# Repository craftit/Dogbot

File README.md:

# Dogbot

[DogBot] is a quadruped robot developed by [React AI] as a platform for researching robotics, AI and more.

The Dogbot repository contains CAD designs, along with software for higher-level systems for control and operation of the [React AI] DogBot robot via [ROS].  It utilises the lower-level motor control firmware in the corresponding [Firmware] repository for interaction with the physical DogBot.

# Installation

This code has been tested for installation and operation on Ubuntu Linux.

[ROS] must be installed; the code has been tested against the Kinetic release.  The repository contains a [catkin](http://wiki.ros.org/catkin) workspace under [Software/ROS](./Software/ROS), which should be built with `catkin build`

You may need to install the packages `ros-kinetic-rosparam-shortcuts ros-kinetic-ros-control ros-kinetic-ros-controllers` 

# Operation via Firmware and ROS

## Home the motors

The motors must be ‘homed’, i.e. know their absolute position, before they can be controlled via the ROS driver, hence they must first be controlled via the UI as described in the [Firmware] repo.

**Note:** complete the Firmware UI steps before starting the ROS components.  The hardware interface node in ROS will send conflicting signals if it is operational while the UI tries to alter the motor positions.

## Quick Start

To get started with ROS control, build and source the code then run `dogbot_hardware.launch`

```bat
cd Software/ROS
catkin build
source devel/setup.bash
roslaunch dogbot_control dogbot_hardware.launch
```

This launches a hardware interface node of type dogbot_control/dogbot_hw_main, which uses the [ros_control](http://wiki.ros.org/controller_manager) package to spawn and interact with ROS controllers.  This provides a framework for different controller types, as well as standardising interactions with Gazebo and RViz.

If you are controlling other equipment you may require a different launch file, such as testrig_hardware.launch

## Further ROS Control

The motors can now be controlled by interacting directly with ROS topics or via ROS nodes. Further details are in the ROS directory [readme file](./Software/ROS)

# Contributing

If you have any problems with the contents of either repository, or have a question about [DogBot], please feel free to [contact us](https://www.reactai.com/)

If you wish to contribute please fork the project on GitHub.  More details on contributing to follow.

# License

details to follow

[DogBot]: https://www.reactai.com/dog-bot/
[React AI]: https://www.reactai.com
[ROS]: http://www.ros.org
[Firmware]: https://github.com/craftit/BMC2-Firmware

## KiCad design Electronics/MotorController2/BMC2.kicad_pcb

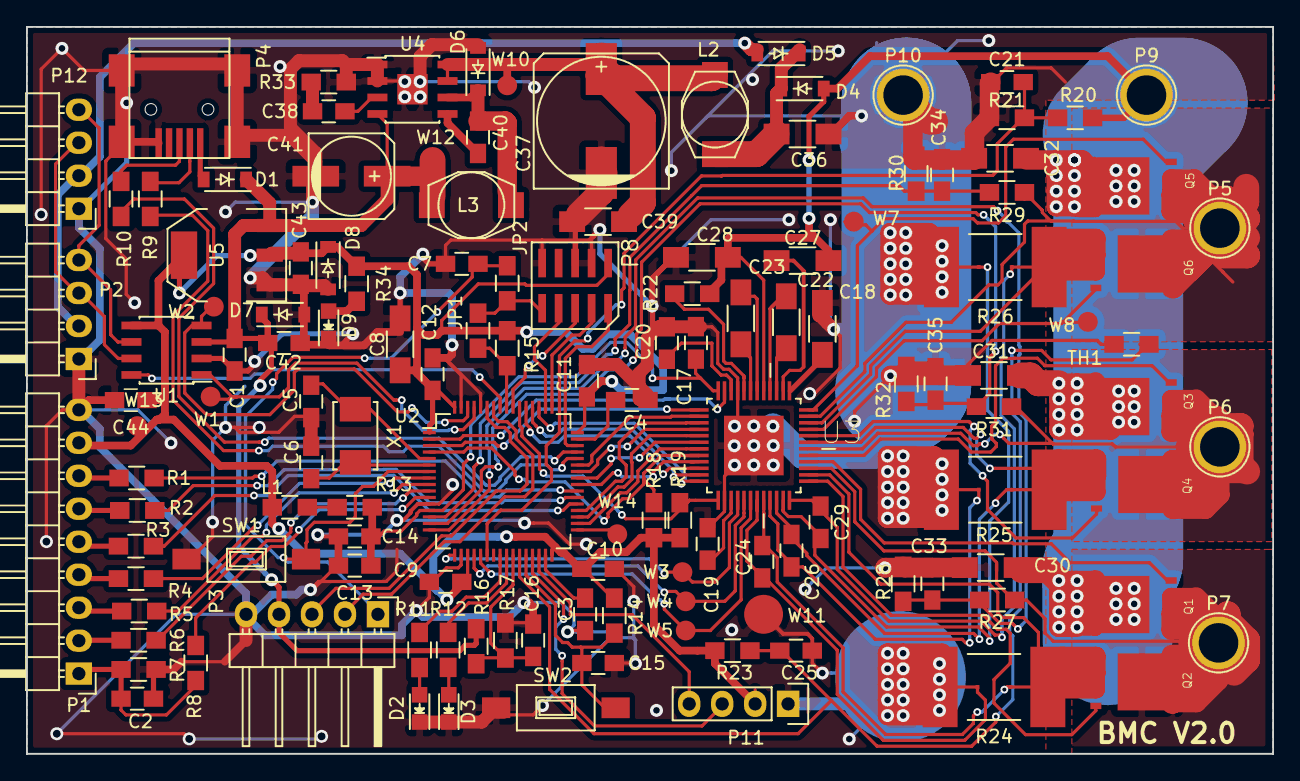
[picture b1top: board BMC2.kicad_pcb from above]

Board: 2 copper layers, 96.0 x 56.0 mm, 131 parts (0 on the bottom side), 109 nets.

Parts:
C1, C44: 0.1uf (6V min); C_0805_HandSoldering
C2: 0.1uF; C_0805_HandSoldering
C3, C4: 2.2uf; C_0805_HandSoldering
C5, C6: 15pF; C_0805_HandSoldering
C7, C10, C11, C12: 100nf; C_0805_HandSoldering
C8: 4.7uf; C_1206_HandSoldering
C9: 100nf 5V; C_0805_HandSoldering
C13: 10nf; C_0805_HandSoldering
C14: 1uf; C_0805_HandSoldering
C15, C16, C21, C25: 0.1uF 5V; C_0805_HandSoldering
C17: 1uF 4V; C_0805_HandSoldering
C18: 1uf 16V; C_1206_HandSoldering
C19, C20: 1uf 6.3V; C_0805_HandSoldering
C22: 0.047uf 90V; C_1206_HandSoldering
C23: 0.047uf 45v; C_1206_HandSoldering
C24, C26: 1nF 5V; C_0805_HandSoldering
C27: 2.2uf 16V; C_1206_HandSoldering
C28: 4.7uF 45V; C_1206_HandSoldering
C29: 1nf 5V; C_0805_HandSoldering
C30, C31, C32: 1uF 50V; C_1206_HandSoldering
C33, C34, C35: 30pF 5V; C_0805_HandSoldering
C36, C39: 220nF 60V; C_1206_HandSoldering
C37: 100uF 60V; c_elec_10x10.5
C38: 22nF 6V; C_0805_HandSoldering
C40, C42: 220nF 6V; C_0805_HandSoldering
C41: 100uF 6V; c_elec_6.3x5.8
C43: 1uF 4V min; C_0805_HandSoldering
D1: 10V; SOD-123
D2: GREEN LED; LED_0805
D3: RED LED; LED_0805
D4, D5: 60V 2A; SOD-123
D6: 50V; SOD-123
D7: 5.4V; SOD-123
D8: 3.6V; SOD-123
D9: LED; LED_0805
JP1: Jumper_NO_Small; R_0805_HandSoldering
JP2: Jumper_NC_Small; R_0805_HandSoldering
L1: 10uH; R_0805_HandSoldering
L2, L3: 47uH; SELF-WE-PD3S
P1: Sensor; Pin_Header_Angled_1x09
P2, P12: CAN; Pin_Header_Angled_1x04
P3: DATA; Pin_Header_Angled_1x05
P4: USB_OTG; USB_Mini-B
P5: PhaseA; 1pin
P6: PhaseB; 1pin
P7: PhaseC; 1pin
P8: CONN_02X05; SMT-HDR-10
P9: VSUPPLY; 1pin
P10: GND; 1pin
P11: I2C; Pin_Header_Straight_1x04
Q1, Q2, Q3, Q4, Q5, Q6: BSC016N06NS; SON127P532X615X110-8N
R1, R2, R3, R4, R5, R6, R8: 1k; R_0805_HandSoldering
R7: 10k; R_0805_HandSoldering
R9, R10: 22R; R_0805_HandSoldering
R11, R12, R22, R34: 100R; R_0805_HandSoldering
R13: 10; R_0805_HandSoldering
R14, R15, R16, R17, R18, R19, R23: 10K; R_0805_HandSoldering
R20, R27, R29, R31: 39K; R_0805_HandSoldering
R21, R28, R30, R32: 3K; R_0805_HandSoldering
R24, R25, R26: R001; R_PSR400_SENSE
R33: 22k; R_0805_HandSoldering
SW1: RESET; SW_SPST_FSMSM
SW2: CAL; SW_SPST_FSMSM
TH1: THERMISTOR; R_0805_HandSoldering
U1: TJA1042T/3; SOIC-8_3.9x4.9mm_Pitch1.27mm
U2: STM32F205RBTx; LQFP-64_10x10mm_Pitch0.5mm
U3: DRV8305; QFP50P900X900X120-49N
U4: IFX91041EJV50; SOIC-8-1EP_3.9x4.9mm_Pitch1.27mm
U5: TC2117-3.3V; SOT-223
W1: CAN_TX; Measurement_Point_Round-SMD-Pad_Small
W2: CAN_RX; Measurement_Point_Round-SMD-Pad_Small
W3: ISenseA; Measurement_Point_Round-SMD-Pad_Small
W4: ISenseB; Measurement_Point_Round-SMD-Pad_Small
W5: ISenseC; Measurement_Point_Round-SMD-Pad_Small
W7: GHA; Measurement_Point_Round-SMD-Pad_Small
W8: GLA; Measurement_Point_Round-SMD-Pad_Small
W10: DSUP; Measurement_Point_Round-SMD-Pad_Small
W11: GND; Measurement_Point_Round-SMD-Pad_Big
W12: 5V; Measurement_Point_Round-SMD-Pad_Small
W13: 3V3; Measurement_Point_Round-SMD-Pad_Small
W14: PB12; Measurement_Point_Round-SMD-Pad_Small
X1: 8MHz; ABM3

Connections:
+3.3VADC: C13.1, C14.1, C17.1, R13.1, U2.13, U3.48
+3V3: C8.1, C9.1, C10.1, C11.1, C12.1, C43.1, C44.1, D8.1, L1.1, P1.8, P8.1, P11.2, R14.1, R15.2, R18.1, R19.1, R23.1, R34.1, U1.5, U2.1, U2.19, U2.32, U2.48, U2.64, U5.2, U5.4, W13.1
+5V: C1.1, C41.1, C42.1, D1.1, D7.1, L3.1, P3.4, R16.1, U1.3, U4.4, U5.3, W12.1
+8V: D5.2, P2.2, P12.2
+36V: C27.2, C28.1, C30.1, C31.1, C32.1, D4.2, P9.1, Q1.5, Q1.6, Q1.7, Q1.8, Q3.5, Q3.6, Q3.7, Q3.8, Q5.5, Q5.6, Q5.7, Q5.8, R20.1, R22.1, U3.41
/Controller/CAN_RX: U1.4, U2.62, W2.1
/Controller/CAN_STBY: U1.8, U2.57
/Controller/CAN_TX: U1.1, U2.61, W1.1
/Controller/EN_GATE: U2.3, U3.1
/Controller/EndStop1: R3.1, U2.37
/Controller/EndStop2: R2.1, U2.38
/Controller/FAULT: R18.2, U2.4, U3.8
/Controller/HallA: R4.1, U2.8
/Controller/HallB: R5.1, U2.9
/Controller/HallC: R6.1, U2.10
/Controller/I2C_SCL: P11.3, U2.29
/Controller/I2C_SDA: P11.4, U2.30
/Controller/INHA: U2.43, U3.2
/Controller/INHB: U2.42, U3.4
/Controller/INHC: U2.41, U3.6
/Controller/INLA: U2.36, U3.3
/Controller/INLB: U2.35, U3.5
/Controller/INLC: U2.34, U3.7
/Controller/ISenseA: U2.17, U3.16, W3.1
/Controller/ISenseB: U2.20, U3.17, W4.1
/Controller/ISenseC: U2.21, U3.18, W5.1
/Controller/Index: R1.1, U2.39
/Controller/MISO: U2.52, U3.11
/Controller/MOSI: U2.53, U3.10
/Controller/PWRGD: R19.2, U2.54, U3.13
/Controller/SCLK: U2.51, U3.12
/Controller/Temp: R8.1, U2.11
/Controller/TempDrv: C25.1, R23.2, TH1.1, U2.27
/Controller/UART_RX: P3.3, U2.59
/Controller/UART_TX: P3.2, U2.58
/Controller/USB_DM: R9.1, U2.44
/Controller/USB_DP: R10.1, U2.45
/Controller/VSenseA: C34.1, R29.2, R30.1, U2.14
/Controller/VSenseB: C35.1, R31.2, R32.1, U2.15
/Controller/VSenseC: C33.1, R27.2, R28.1, U2.16
/Controller/VSenseSupply: C21.1, R20.2, R21.1, U2.22
/Controller/sSCS: U2.40, U3.9
/power/PhaseA: P5.1, Q5.1, Q5.2, Q5.3, Q6.5, Q6.6, Q6.7, Q6.8, R29.1, U3.35
/power/PhaseB: P6.1, Q3.1, Q3.2, Q3.3, Q4.5, Q4.6, Q4.7, Q4.8, R31.1, U3.30
/power/PhaseC: P7.1, Q1.1, Q1.2, Q1.3, Q2.5, Q2.6, Q2.7, Q2.8, R27.1, U3.27
/power/WAKE: U2.2, U3.47
GND: C1.2, C2.2, C3.2, C4.2, C5.2, C6.2, C7.2, C8.2, C9.2, C10.2, C11.2, C12.2, C13.2, C14.2, C15.2, C16.2, C17.2, C18.2, C19.2, C20.2, C21.2, C25.2, C28.2, C30.2, C31.2, C32.2, C33.2, C34.2, C35.2, C36.2, C37.2, C39.2, C41.2, C42.2, C43.2, C44.2, D2.1, D3.1, D6.2, D7.2, D8.2, D9.1, P1.9, P2.1, P3.5, P4.5, P4.6, P8.3, P8.5, P8.9, P10.1, P11.1, P12.1, R7.2, R17.2, R21.2, R24.4, R25.4, R26.4, R28.2, R30.2, R32.2, R33.2, SW1.1, SW2.2, TH1.2, U1.2, U2.12, U2.18, U2.60, U2.63, U3.14, U3.45, U3.49, U4.1, U4.2, U4.9, U5.1, W11.1
NRST: C7.1, JP2.2, P3.1, SW1.2, U2.7
unnamed: C2.1, P1.1, R7.1, R8.2
unnamed: C3.1, U2.31
unnamed: C4.1, U2.47
unnamed: C5.1, U2.5, X1.1
unnamed: C6.1, U2.6, X1.2
unnamed: C15.1, R14.2, SW2.1, U2.28
unnamed: C16.1, R16.2, R17.1, U2.26
unnamed: C18.1, U3.37
unnamed: C19.1, U3.15
unnamed: C20.1, U3.46
unnamed: C22.1, U3.39
unnamed: C22.2, U3.40
unnamed: C23.1, U3.43
unnamed: C23.2, U3.42
unnamed: C24.1, R24.2, U3.20
unnamed: C24.2, R24.3, U3.19
unnamed: C26.1, R25.2, U3.22
unnamed: C26.2, R25.3, U3.21
unnamed: C27.1, U3.38
unnamed: C29.1, R26.2, U3.24
unnamed: C29.2, R26.3, U3.23
unnamed: C36.1, D4.1, D5.1, L2.2
unnamed: C37.1, C39.1, L2.1, U4.7, U4.8, W10.1
unnamed: C38.1, U4.3
unnamed: C38.2, R33.1
unnamed: C40.1, U4.5
unnamed: C40.2, D6.1, L3.2, U4.6
unnamed: D1.2, P4.1
unnamed: D2.2, R11.2
unnamed: D3.2, R12.2
unnamed: D9.2, R34.2
unnamed: JP1.1, R15.1, U2.56
unnamed: JP1.2, JP2.1, P8.10
unnamed: L1.2, R13.2
unnamed: P1.2, R6.2
unnamed: P1.3, R5.2
unnamed: P1.4, R4.2
unnamed: P1.5, R3.2
unnamed: P1.6, R2.2
unnamed: P1.7, R1.2
unnamed: P4.2, R9.2
unnamed: P4.3, R10.2
unnamed: P8.2, U2.46
unnamed: P8.4, U2.49
unnamed: P8.6, U2.55
unnamed: P8.8, U2.50
unnamed: P2.3, P12.3, U1.7
unnamed: P2.4, P12.4, U1.6
unnamed: Q1.4, U3.28
unnamed: Q2.1, Q2.2, Q2.3, R24.1, U3.26
unnamed: Q2.4, U3.25
unnamed: Q3.4, U3.29
unnamed: Q4.1, Q4.2, Q4.3, R25.1, U3.31
unnamed: Q4.4, U3.32
unnamed: Q5.4, U3.36, W7.1
unnamed: Q6.1, Q6.2, Q6.3, R26.1, U3.34
unnamed: Q6.4, U3.33, W8.1
unnamed: R11.1, U2.24
unnamed: R12.1, U2.25
unnamed: R22.2, U3.44
unnamed: U2.33, W14.1

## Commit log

2017-07-20 Added current CAD and motor controller schematics.
2017-07-20 Add pointer to motor controller firmware.
2017-07-21 Add dogbot urdf file.
2017-07-21 Add license file.
2017-08-10 created Plate_001 in FreeCAD
2017-08-11 Added CAD for new split delvis design
2017-08-13 Add access holes.
2017-08-17 Add place to put cable tie.
2017-08-17 Add standoff for motor driver mounts.
2017-08-27 Updates and new parts.
2017-08-29 Add capacitor connection cover, and increase number of positions for end stop sensors.
2017-08-31 Add add lenght pad for rods.
2017-08-31 Move thermocouple hole so the screw hole is accessible for fixing, add leg spacer, fix battery mount.
2017-09-04 Add place for temprature sensor in motor mount. Make sure there is a cable clamp for data wires.
2017-09-04 Move boards to give more clearence for the connectors on the body mounted controllers.
2017-09-05 Add missing chamfer.
2017-09-10 Add temprature sensor cover, fix motor drive mount cover.
2017-09-11 Add other side of battery mount.
2017-09-15 Notes on states of driver boards.
2017-09-19 Change hole spacing on pelvis.
2017-09-19 Updated Pelvis with chamfers and fillets.
2017-09-25 New experimental lightweight parts.
2017-09-26 Change carrier to 3mm, add FixedRing 1_5.
2017-09-29 new motos cowling for large motor and bearing housings for test jig
2017-09-29 Allow link between servos
2017-09-29 Carrier renamed and increased spacing for washers.
2017-09-29 motor adapter for propdrive motor
2017-10-01 Work on new gearbox.
2017-10-02 Misc fixes.
2017-10-03 Fix overhang problem in rod recess.
2017-10-03 Tweak dimensions.
2017-10-06 large motor cowling - mods for hall sensor
2017-10-06 servo blinding + battery mount clips
2017-10-07 Fixes for printability.
2017-10-10 PD5060 sensor mount, and PCB version.
2017-10-13 changes for 15mm CF rods - some still to do, see notes
2017-10-17 Make parts the same size.
2017-10-18 Fix short tails, add wide-long motor adaptor.
2017-10-18 Add version of knee with end stops.
2017-10-24 2D drawing to test gearbox spacing
2017-10-25 Knee updates, and add altenate drive link design.
2017-10-27 updates for 15.5mm rod recess
2017-10-30 Minor tweeks.
2017-11-03 new battery + breaker mount
2017-11-09 1.5 module planets
2017-11-20 1.45module sun gear
2017-12-05 Work in progress for the driver node.
2017-12-08 More work on ros control.
2017-12-08 Fixes.
2017-12-22 Update interface code to synchronise timings.
2018-01-10 Updates for changes to driver code.
2018-01-12 updates to ros cmake files
2018-01-12 hardware interface pickup file location from launch file via parameter server
2018-01-15 change config location
2018-01-15 added separate controllers
2018-01-23 Update README.md
    First pass readme, still needs e.g. licence details
2018-01-25 keyboard ROS controller work in progress
2018-01-31 readme updates and test-rig config files
2018-02-06 updating README for prerequisites
2018-03-01 Fix typo.
2018-03-29 refactor of packages
2018-03-29 Add some gait generation.
2018-03-29 refactored gazebo sim
2018-04-06 Add walking.
2018-04-08 added joint movement demo to gazebo
2018-04-11 Add initial parts of data recorder.
2018-04-12 Improved logging.
2018-04-12 Log joint velocity estimates.
2018-04-13 Add more information about the joint.
2018-04-13 Tinker with walk parameters.
2018-04-16 updated install notes
2018-04-27 Updates for logging.
2018-04-30 Rename some classes to avoid conflicts.
2018-05-02 Add float32_2 type.
2018-05-03 Start on COG correction.
2018-05-09 Fix for change to coordinate system.
